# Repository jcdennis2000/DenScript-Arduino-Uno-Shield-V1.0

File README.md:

# DenScript-Arduino-Uno-Shield-V1.0

The DenScript Arduino Uno Shield is the best way to integrate DenScript Modules with your Arduino!

The Shield breaks out all of the digital and analogue pins into the DenScript colour Coded format. The 6 PWM Pins on the Arduino Uno are also broken out a second time, but with a twist, they have the orange pins for power, meaning VIN, so you can power higher power loads. There is also a Pixel header, connected to digital pin 8. Finally, there are power pins broken out for GND (Black), 5V (Red) and VIN (Orange), and a Reset Button.

The board has a large section at the front missing to ensure it will not interfere with any power jacks, USB connectors or Ethernet sockets you may have on your Arduino.

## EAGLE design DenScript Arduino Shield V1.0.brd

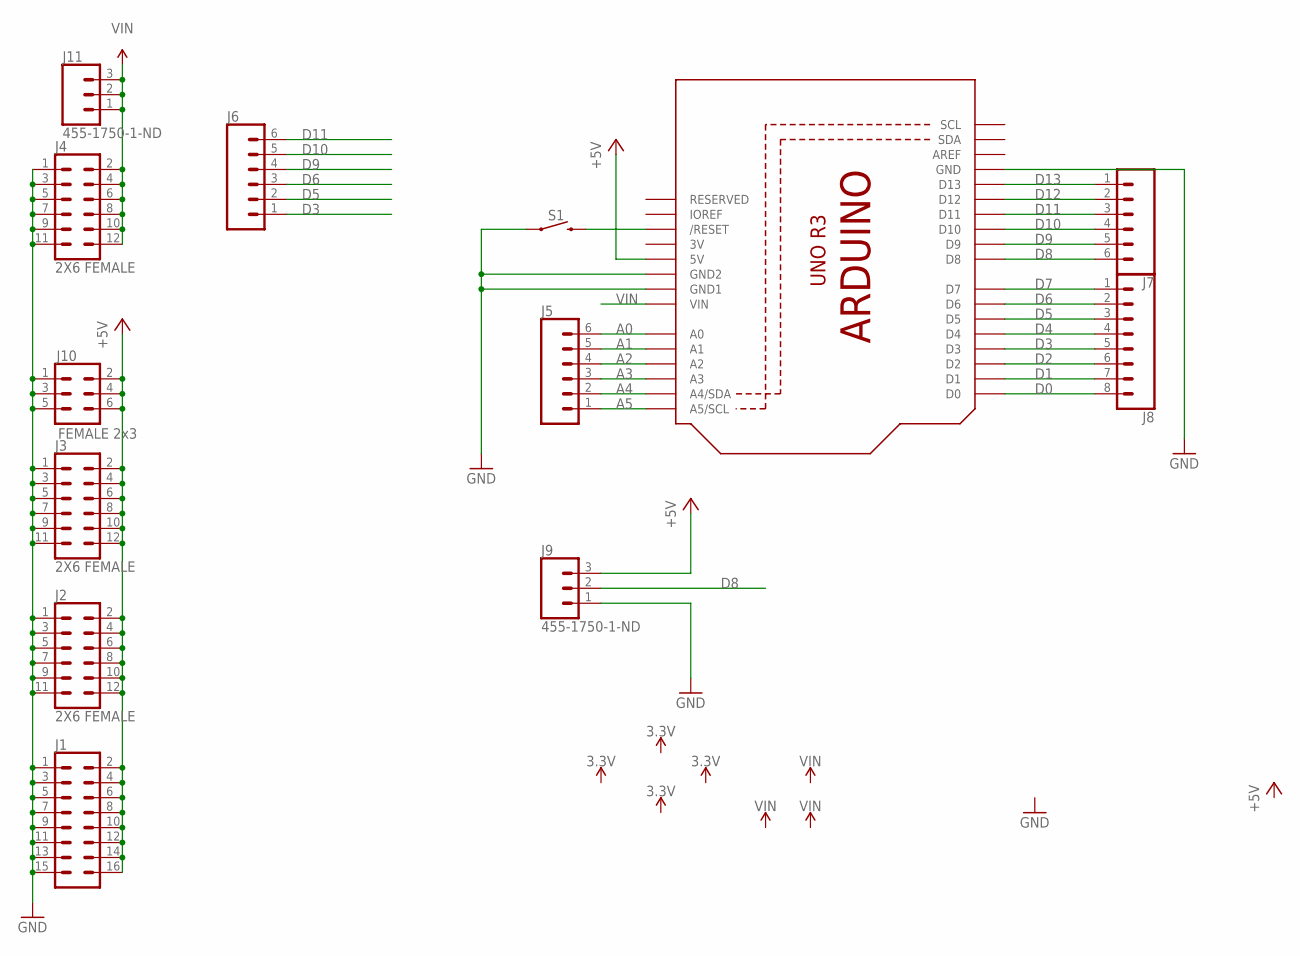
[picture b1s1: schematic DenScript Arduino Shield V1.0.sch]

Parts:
J1: CONN_08X2_HEADER; 2X8
J2, J3, J4: 2X6 FEMALE; 2X6
J5, J6, J7: CONN_06SILK_FEMALE_PTH; 1X06
J8: CONN_08"; 1X08
J9, J11: 455-1750-1-ND; 1X03
J10: FEMALE 2x3; 2X3
S1: MOMENTARY-SWITCH-SPST-PTH-6.0MM; TACTILE_SWITCH_PTH_6.0MM
U1: ARDUINOR3-BPLACE

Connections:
3V: U1.3V
+5V: J1.2, J1.4, J1.6, J1.8, J1.10, J1.12, J1.14, J1.16, J2.2, J2.4, J2.6, J2.8, J2.10, J2.12, J3.2, J3.4, J3.6, J3.8, J3.10, J3.12, J9.3, J10.2, J10.4, J10.6, U1.5V
A0: J5.6, U1.A0
A1: J5.5, U1.A1
A2: J5.4, U1.A2
A3: J5.3, U1.A3
A4: J5.2, U1.A4 (A4/SDA)
A5: J5.1, U1.A5 (A5/SCL)
D0: J8.8, U1.D0
D1: J8.7, U1.D1
D2: J8.6, U1.D2
D3: J6.1, J8.5, U1.D3
D4: J8.4, U1.D4
D5: J6.2, J8.3, U1.D5
D6: J6.3, J8.2, U1.D6
D7: J8.1, U1.D7
D8: J7.6, J9.2, U1.D8
D9: J6.4, J7.5, U1.D9
D10: J6.5, J7.4, U1.D10
D11: J6.6, J7.3, U1.D11
D12: J7.2, U1.D12
D13: J7.1, U1.D13
GND: J1.1, J1.3, J1.5, J1.7, J1.9, J1.11, J1.13, J1.15, J2.1, J2.3, J2.5, J2.7, J2.9, J2.11, J3.1, J3.3, J3.5, J3.7, J3.9, J3.11, J4.1, J4.3, J4.5, J4.7, J4.9, J4.11, J9.1, J10.1, J10.3, J10.5, S1.1, U1.GND, U1.GND1, U1.GND2
unnamed: S1.3 (2), U1.RESET (/RESET)
VIN: J4.2, J4.4, J4.6, J4.8, J4.10, J4.12, J11.1, J11.2, J11.3, U1.VIN

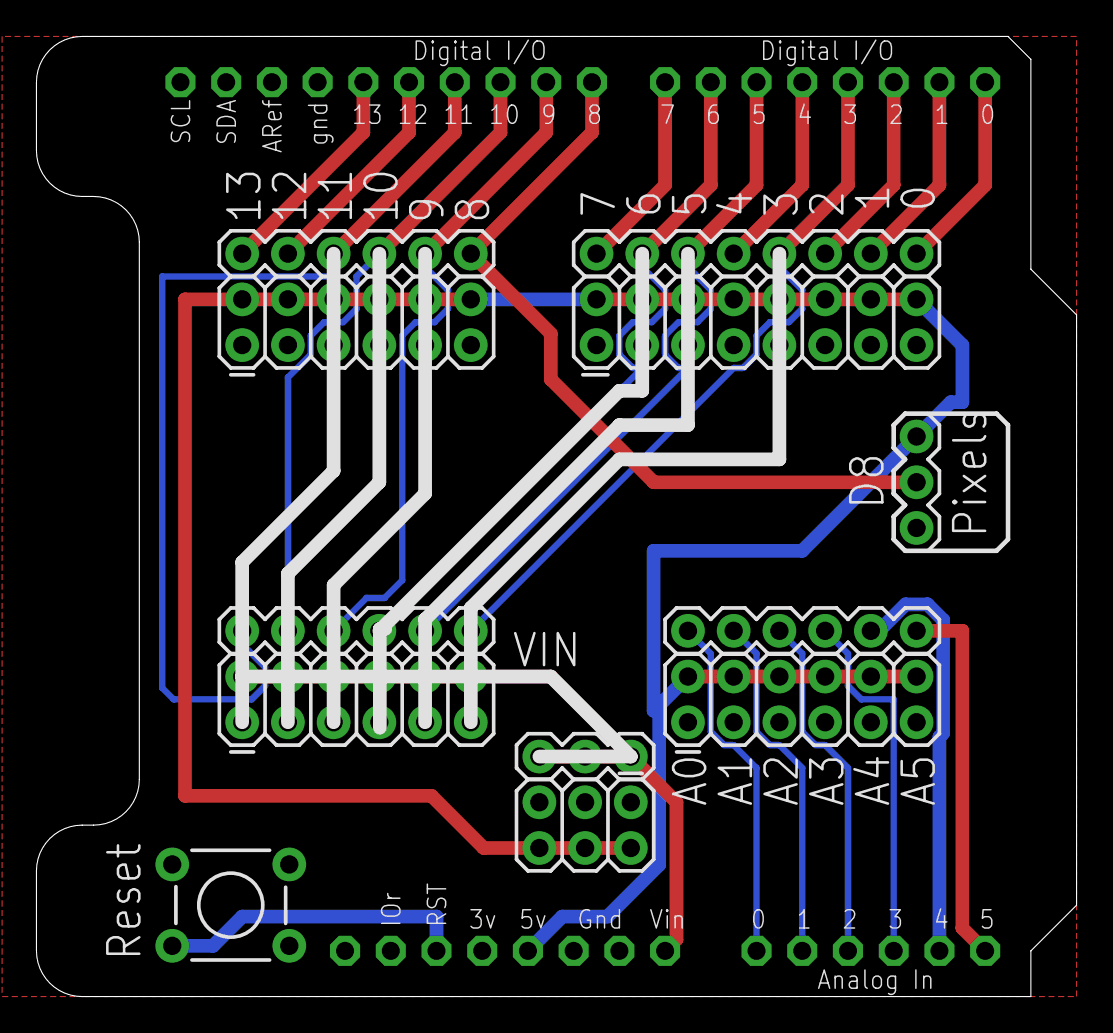
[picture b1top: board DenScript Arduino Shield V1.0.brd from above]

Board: 2 copper layers, 57.8 x 53.3 mm, 13 parts (0 on the bottom side), 24 nets.

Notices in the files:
DenScript Arduino Shield V1.0.brd:
Dennistries Ltd (c) 2019
parts and their libraries:
SparkFun-Connectors: Licensing: Creative Commons ShareAlike 4.0 International - https://creativecommons.org/licenses/by-sa/4.0
